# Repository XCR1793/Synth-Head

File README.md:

# Synth Head
To create an open source suit which can be worn by an individual and customised to their will. It also must be constructed in such a way that an average human could build it within a reasonable budget and time. The suit must be modular whilst remaining safe for the user to operate. The software must be easy to configure for any individual and has capability to modify without the need to always reflashing its firmware. The project was created according to this standard however, it has evolved over time to be more of a testing ground for sensors and other features of the like as I will continue this along with other projects I have due to compatibility.

## Overview
This project is always in the works and will be updated. Although regular updates are not possible due to me still being in uni, I will do what I can. This repo is basically a better version of the other repo and a true migration as the old one due to its structure. The reason for it being a new repo rather then just a fix is cause the title changed so the old link wouldn't have worked anyway. The current design is DX which stands for Design 10 as it is the 10th time the base shape has changed, the .3 at the end is an iterator for which version were on.

### Features
* <strong style='color: #99ccff;'>Vacuum Formed Visor</strong> allows the user to see out of a clear shell rather then the previous mesh version which caused chromatic abberation, preventing the true colours of the display from emiting through the visor properly.
* <strong style='color: #99ccff;'>Detachable Substructure</strong> which conformes to the visor ridge provides an easy to modify platform to which different displays, sensors and other modules.
* <strong style='color: #99ccff;'>Builtin Head Restraint</strong> was designed to hold in an average head with relatively high pressure, although the pressure seems like it cause pain, the addition of a foam pad mitigates this and is actually comfortable to wear.
* <strong style='color: #99ccff;'>Silent Slim Jaw Mount</strong> of around 6mm in total thickness is directly integrated to the shell.
* <strong style='color: #99ccff;'>Snoot Sensors</strong> All of the sensors and modules are attached directly into the detachable substructure and can easily be replaced and upgraded as needed, many of which includes: Boop detection, snoot holding detection & IMUs.
* <strong style='color: #99ccff;'>Ventillation</strong> is key to an alive and well user, there are 2 fans located below the tongue which negatively ventillates the user.

### In the works
* The visor edge and mating surface will be changed due to it currently resulting in an uneven edge to edge connection.
* The builtin head restraint will also be upgraded, although the system works it is not the best designed as it is currently difficult to put the pins in place.
* Electronics & other cabling will be hidden in the final release as it is not compact due to the Rushed version built for speed and prototyping rather then stability.
* ARCOS migration is still under play, the entire library is basically being rewritten slowly so it runs faster with more features. The library is currently not accessable as it is privated but it will be released with the release of the synth head 10.3.
* <strong style='color: #ffb3ff;'>Feature Inclusion:</strong> Cable management
* <strong style='color: #ffb3ff;'>Feature Inclusion:</strong> Visor Edge Alignment Upgrade
* <strong style='color: #ffb3ff;'>Feature Inclusion:</strong> Ventillation Upgrade
* <strong style='color: #ffb3ff;'>Feature Inclusion:</strong> Jaw Mount Upgrade (Attached to head restraint)
* <strong style='color: #ffb3ff;'>Feature Inclusion:</strong> Lighter Frame
* <strong style='color: #ffb3ff;'>Feature Inclusion:</strong> Custom PCB (Control Board, Power & Sensors)

### Roadmap
* <strong style='color: #99ff99;'>Milestone:</strong> [Synth Head DX](/Archives/DX/README.md)
* <strong style='color: #99ff99;'>Milestone:</strong> [Synth Head DX.1](/Archives/DX.1/README.md)
* <strong style='color: #99ff99;'>Milestone:</strong> [Synth Head DX.2 Rushed](/Archives/DX.2/README.md)
* <strong style='color: #99ff99;'>Milestone:</strong> [Synth Head DX.3 Rushed](/Archives/DX.3/README.md)
* <strong style='color: #99ff99;'>Milestone:</strong> Properly Structured Github

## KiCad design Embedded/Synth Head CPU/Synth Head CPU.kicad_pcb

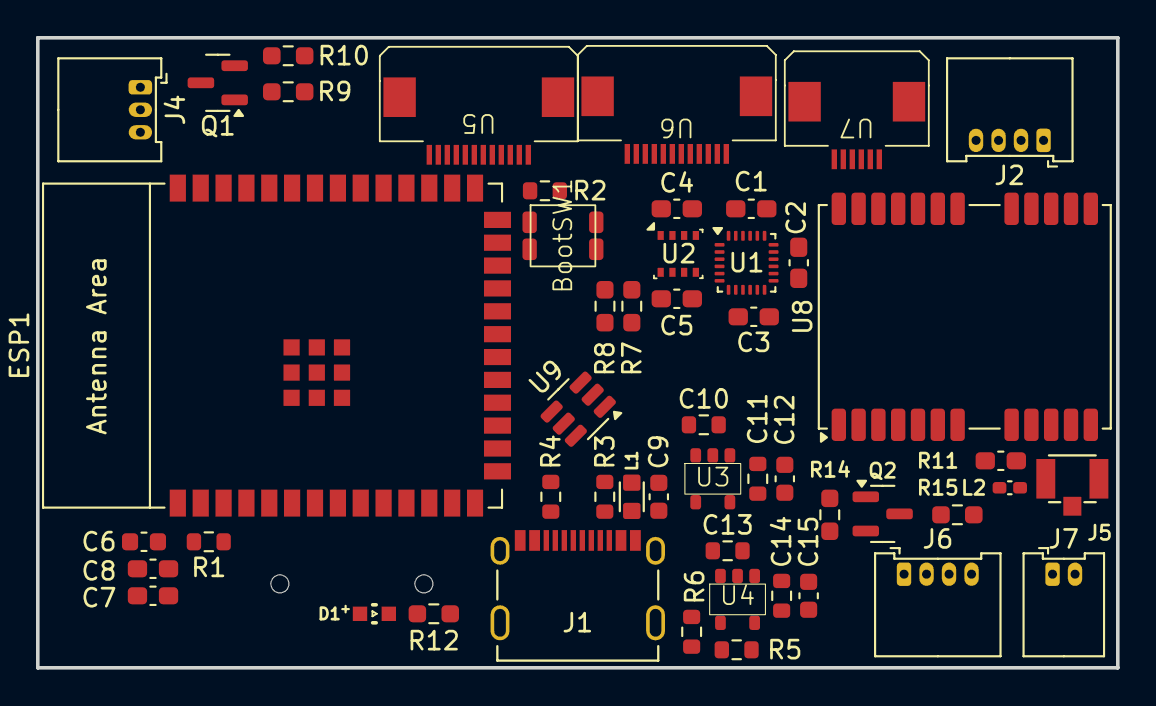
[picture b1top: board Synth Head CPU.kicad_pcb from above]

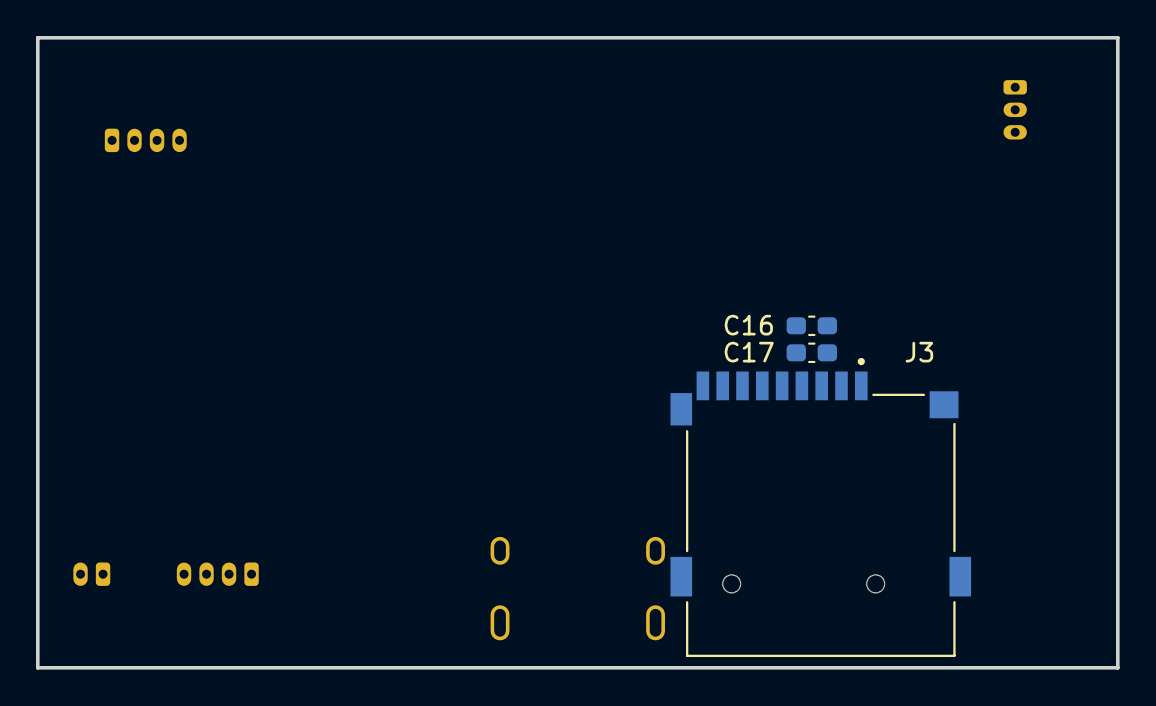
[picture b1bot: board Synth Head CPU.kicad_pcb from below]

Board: 2 copper layers, 60.0 x 35.0 mm, 54 parts (3 on the bottom side), 23 nets, no tracks yet.

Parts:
BootSW1: SW_Push; Button-R-667843
C1, C2, C3, C8, C17: 0.1uF; C_0603_1608Metric_Pad1.08x0.95mm_HandSolder
C4, C5: 100nF; C_0603_1608Metric_Pad1.08x0.95mm_HandSolder
C6: 1uF; C_0603_1608Metric
C7, C16: 22uF; C_0603_1608Metric_Pad1.08x0.95mm_HandSolder
C9, C12, C15: 10uF; C_0603_1608Metric
C10, C11, C13, C14: 1uF; R_0603_1608Metric
D1: WL-SMCW_0603
ESP1: ESP32-S3-WROOM-1
J1: 10171746-00021LF; AMPHENOL_10171746-00021LF
J2: JST [C]; Molex_PicoBlade_53048-0410_1x04_P1.25mm_Horizontal
J3: MSD-1-A; CUI_MSD-1-A
J4: JST [N]; Molex_PicoBlade_53048-0310_1x03_P1.25mm_Horizontal
J5: U.FL-R-SMT-1_10_; HRS_U.FL-R-SMT-1_10_
J6: Pogo JST; Molex_PicoBlade_53048-0410_1x04_P1.25mm_Horizontal
J7: Pogo JST; Molex_PicoBlade_53048-0210_1x02_P1.25mm_Horizontal
L1: MPZ1608S601ATA00; INDC1608X95N
L2: LQG15HS27NJ02; L_0402_1005Metric_Pad0.77x0.64mm_HandSolder
Q1, Q2: BSS138; SOT-23
R1, R2: 10K; R_0603_1608Metric
R3, R4: 5.1K; R_0603_1608Metric
R5: 75K; R_0603_1608Metric
R6: 60K; R_0603_1608Metric
R7, R8, R9, R10, R14, R15: 10K; R_0603_1608Metric_Pad0.98x0.95mm_HandSolder
R11: 10; C_0603_1608Metric_Pad1.08x0.95mm_HandSolder
R12: 65; R_0603_1608Metric_Pad0.98x0.95mm_HandSolder
U1: ICM-20948; InvenSense_QFN-24_3x3mm_P0.4mm
U2: BME280; Bosch_LGA-8_2.5x2.5mm_P0.65mm_ClockwisePinNumbering
U3: AP7366-33W5-7; AP7366
U4: AP7366-W5-7; AP7366
U5: FFC [G]; FFC Aliexpress 0.5mm 12P
U6: FFC [M]; FFC Aliexpress 0.5mm 12P
U7: FFC [K]; FFC Aliexpress 0.5mm 6P
U8: NEO-M8M; ublox_NEO
U9: SRV05-4; SOT-23-6

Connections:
3V3 Jaw LEDS: Q2.2 (S), R14.2
3V3 Neck LEDS: Q1.2 (S), R9.2
+1V8: C1.2, C14.1, C15.1, R5.1, U1.8 (VDDIO), U1.22 (~CS), U4.5 (Vout)
+3V3: C2.1, C4.2, C5.1, C7.1, C8.1, C11.1, C12.1, C16.1, C17.1, D1.2, ESP1.2 (3V3), J3.4 (VDD), Q1.1 (G), Q2.1 (G), R1.1, R2.1, R7.1, R8.1, R9.1, R14.1, U1.13 (VDD), U2.2 (CSB), U2.6 (VDDIO), U2.8 (VDD), U3.5 (Vout), U8.23 (VCC)
+5V: J1.A4_B9 (VBUS_A), J1.B4_A9 (VBUS_B), J2.2, J2.3, J4.2, J7.1, J7.2, L1.1, R10.1, R15.1, U5.5, U5.8, U6.5, U6.8, U9.5 (VP)
/1V8 Regulator/Vin: C9.1, C10.1, C13.1, L1.2, U3.1 (VCC), U3.3 (EN), U4.1 (VCC), U4.3 (EN)
GND: BootSW1.2, C1.1, C2.2, C3.2, C4.1, C5.2, C6.1, C7.2, C8.2, C9.2, C10.2, C11.2, C12.2, C13.2, C14.2, C15.2, C16.2, C17.2, ESP1.1 (GND), ESP1.40 (GND), ESP1.41 (GND), J1.A1_B12 (GND_A), J1.B1_A12 (GND_B), J2.1, J2.4, J3.6 (VSS), J3.G1 (COVER_GND), J3.G2 (COVER_GND__1), J3.G3 (COVER_GND__2), J3.G4 (COVER_GND__3), J4.1, J5.1, J6.1, J6.4, R3.2, R4.2, R6.2, R12.2, U1.9 (SDO/AD0), U1.18 (GND), U1.20 (GND), U2.1 (GND), U2.5 (SDO), U2.7 (GND), U3.2 (GND), U4.2 (GND), U5.1, U5.3, U5.10, U5.12, U6.1, U6.2, U6.3, U6.10, U6.11, U6.12, U7.1, U7.6, U8.7 (VDD_USB), U8.10 (GND), U8.12 (GND), U8.13 (GND), U8.24 (GND), U9.2 (VN)
Jaw LEDS: J6.2, J6.3, Q2.3 (D), R15.2
Neck LEDS: J4.3, Q1.3 (D), R10.2
unnamed: D1.1, R12.1
unnamed: C6.2, ESP1.3 (EN), R1.2
unnamed: BootSW1.1, ESP1.27 (GPIO0/BOOT), R2.2
unnamed: J1.A5 (CC1), R4.1
unnamed: J1.B5 (CC2), R3.1
unnamed: L2.1, R11.2
unnamed: C3.1, U1.10 (REGOUT)
unnamed: R5.2, R6.1, U4.4 (ADJ)
unnamed: J5.2, L2.2, U8.11 (RF_IN)
unnamed: R11.1, U8.9 (VCC_RF)
SCL: R7.2, U1.23 (SCL/SCLK), U2.4 (SCK), U8.19 (SCL/SPI_CLK)
SDA: R8.2, U1.24 (SDA/SDI), U2.3 (SDI), U8.18 (SDA/~SPI_CS)
USB +: ESP1.14 (GPIO20/U1CTS/ADC2_CH9/CLK_OUT1/USB_D+), J1.A6 (DP1), J1.B6 (DP2), U7.3, U9.1 (IO1)
USB -: ESP1.13 (GPIO19/U1RTS/ADC2_CH8/CLK_OUT2/USB_D-), J1.A7 (DN1), J1.B7 (DN2), U7.4, U9.4 (IO3)

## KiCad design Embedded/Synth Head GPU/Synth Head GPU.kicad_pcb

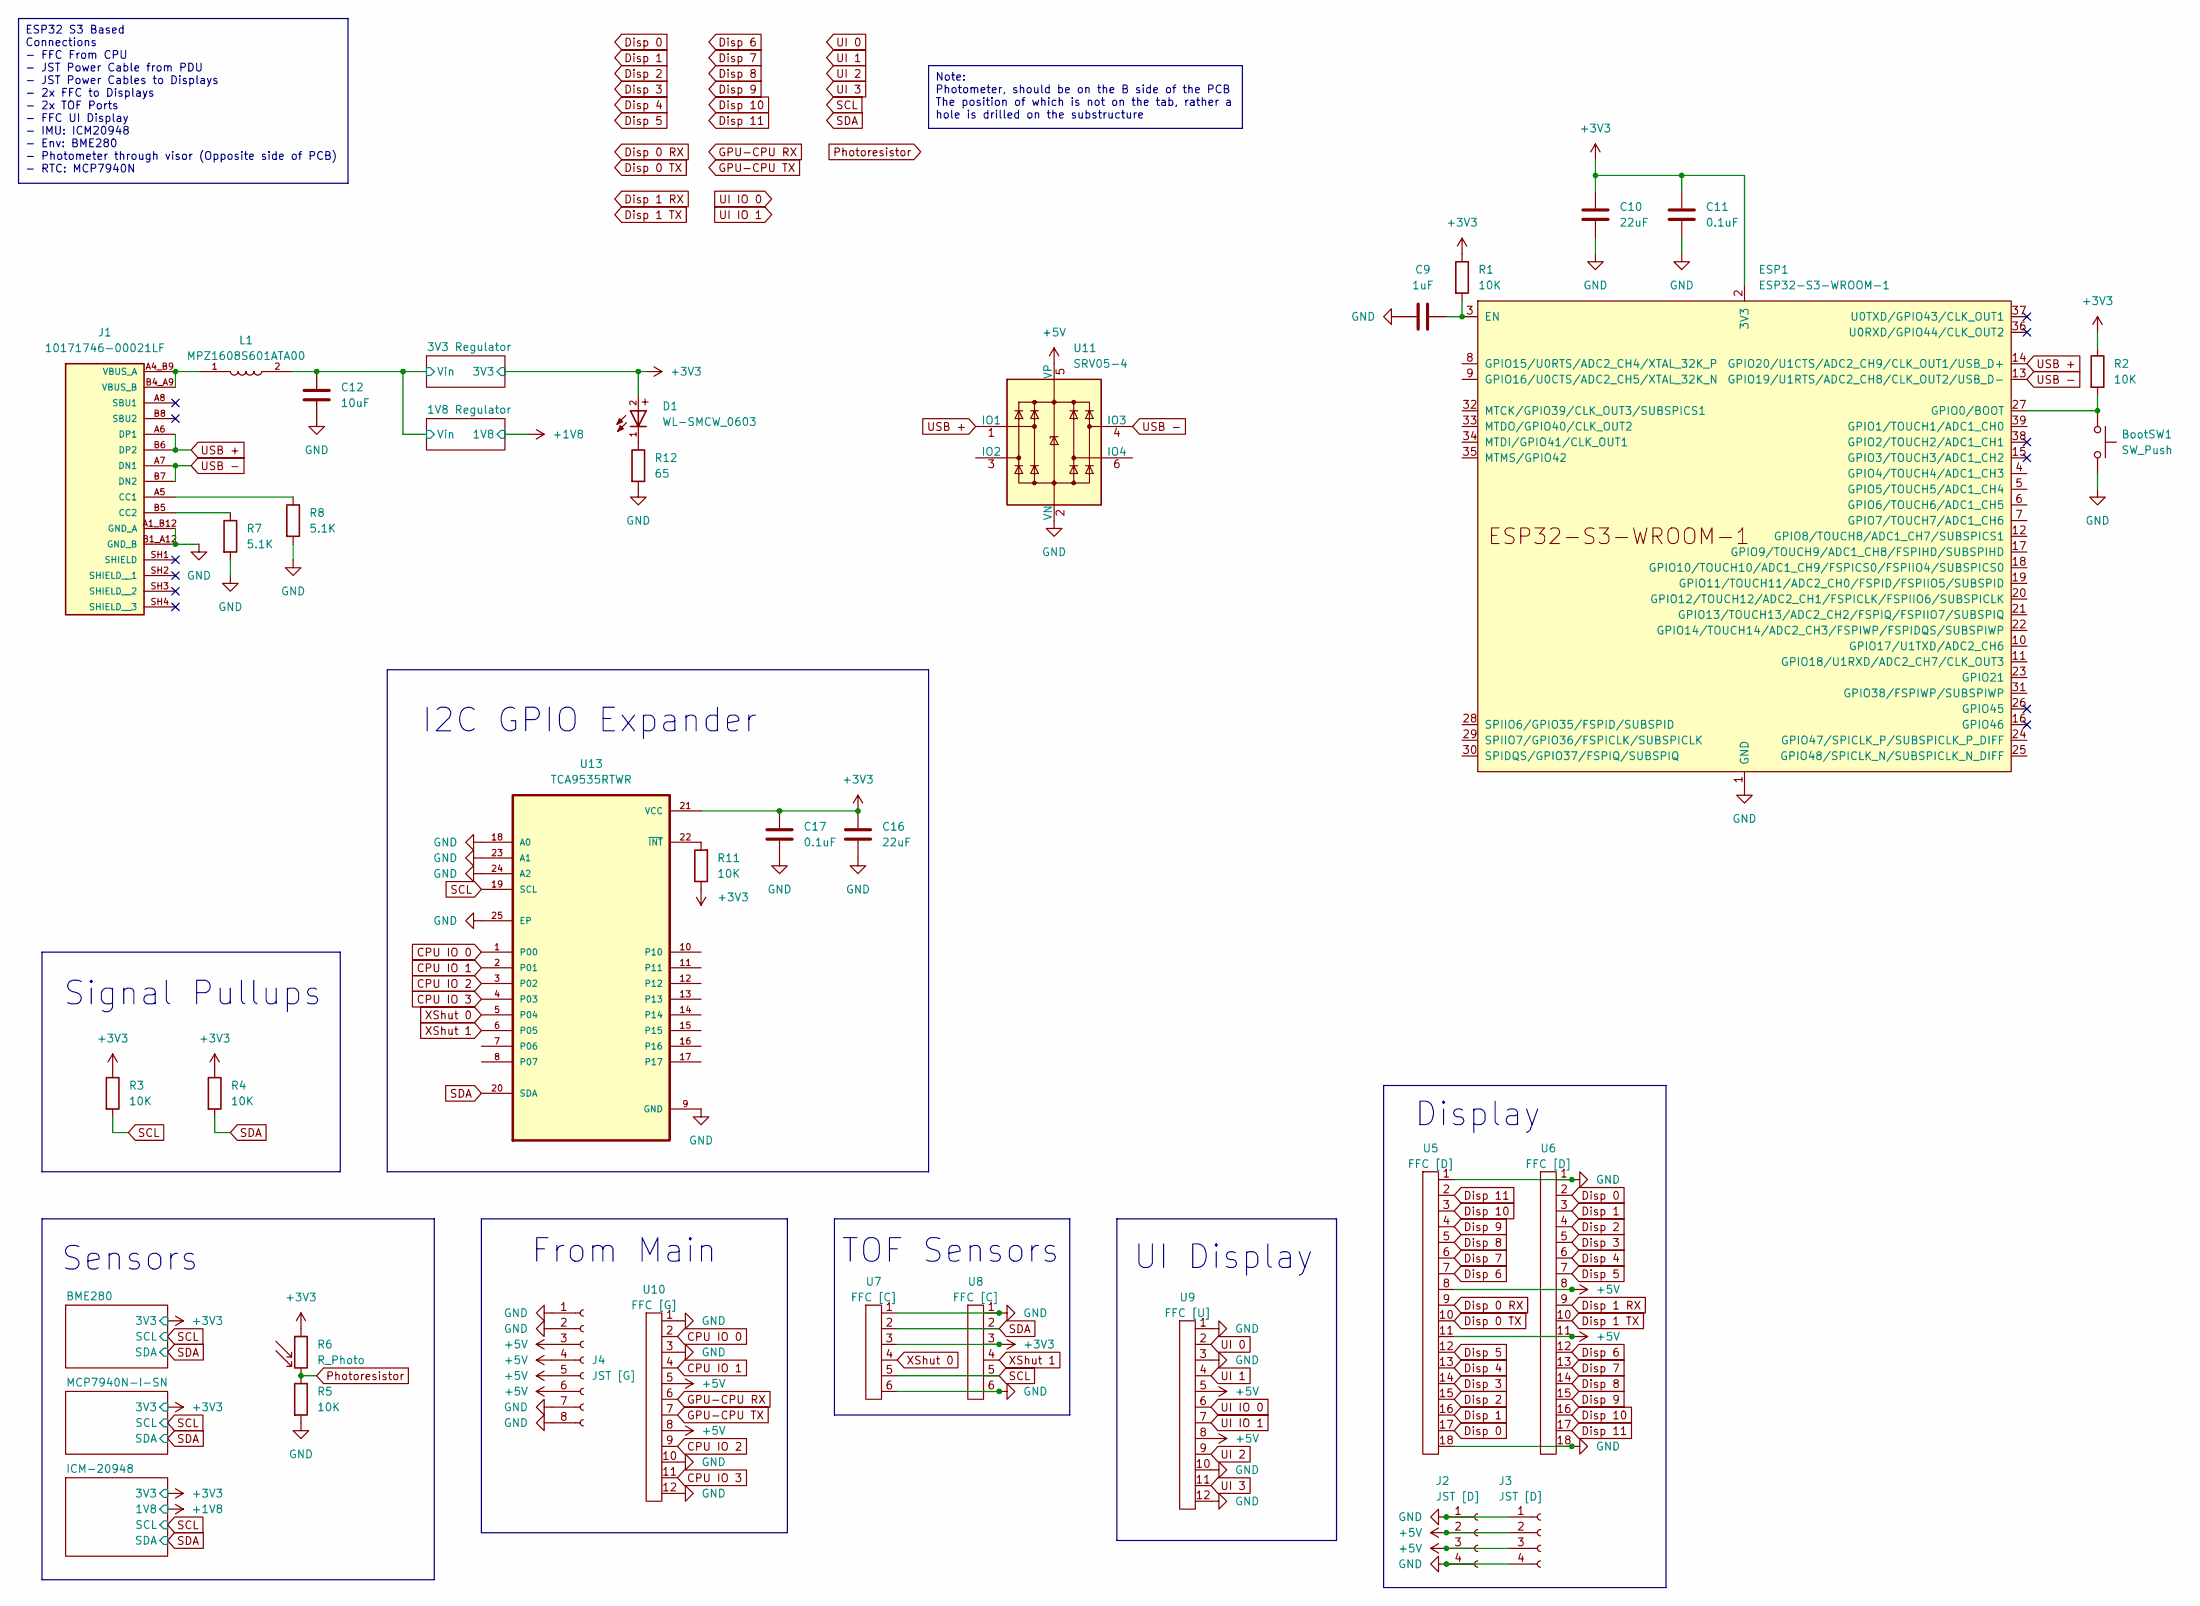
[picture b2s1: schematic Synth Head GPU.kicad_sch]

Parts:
BootSW1: SW_Push; Button-R-667843
C9: 1uF; C_0603_1608Metric
C10, C16: 22uF; C_0603_1608Metric_Pad1.08x0.95mm_HandSolder
C11, C17: 0.1uF; C_0603_1608Metric
C12: 10uF; C_0603_1608Metric
D1: WL-SMCW_0603
ESP1: ESP32-S3-WROOM-1; ESP32-S3-WROOM-1U
J1: 10171746-00021LF; AMPHENOL_10171746-00021LF; PARTREV A
J2, J3: JST [D]; Molex_PicoBlade_53048-0410_1x04_P1.25mm_Horizontal
J4: JST [G]; PinHeader_1x08_P2.54mm_Horizontal
L1: MPZ1608S601ATA00; INDC1608X95N
R1, R2, R11: 10K; R_0603_1608Metric
R3, R4, R5: 10K; R_0603_1608Metric_Pad0.98x0.95mm_HandSolder
R6: R_Photo; Photoresistor Aliexpress
R7, R8: 5.1K; R_0603_1608Metric
R12: 65; R_0603_1608Metric_Pad0.98x0.95mm_HandSolder
U5, U6: FFC [D]; FFC Aliexpress 0.5mm 18P
U7, U8: FFC [C]; FFC Aliexpress 0.5mm 6P
U9: FFC [U]; FFC Aliexpress 0.5mm 12P
U10: FFC [G]; FFC Aliexpress 0.5mm 12P
U11: SRV05-4; SOT-23-6
U13: TCA9535RTWR; QFN50P400X400X80-25N

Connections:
+3V3: C10.1, C11.1, C16.1, C17.1, D1.2, ESP1.2 (3V3), R1.1, R2.1, R3.1, R4.1, R6.1, R11.1, U7.3, U8.3, U13.21 (VCC); also elsewhere on the board
+5V: J2.2, J2.3, J3.2, J3.3, J4.3, J4.4, J4.5, J4.6, U5.8, U5.11, U6.8, U6.11, U9.5, U9.8, U10.5, U10.8, U11.5 (VP)
/1V8 Regulator/Vin: C12.1, L1.2; also elsewhere on the board
CPU IO 0: U10.2, U13.1 (P00)
CPU IO 1: U10.4, U13.2 (P01)
CPU IO 2: U10.9, U13.3 (P02)
CPU IO 3: U10.11, U13.4 (P03)
Disp 0: U5.17, U6.2
Disp 0 RX: U5.9
Disp 0 TX: U5.10
Disp 1: U5.16, U6.3
Disp 1 RX: U6.9
Disp 1 TX: U6.10
Disp 2: U5.15, U6.4
Disp 3: U5.14, U6.5
Disp 4: U5.13, U6.6
Disp 5: U5.12, U6.7
Disp 6: U5.7, U6.12
Disp 7: U5.6, U6.13
Disp 8: U5.5, U6.14
Disp 9: U5.4, U6.15
Disp 10: U5.3, U6.16
Disp 11: U5.2, U6.17
GND: BootSW1.2, C9.1, C10.2, C11.2, C12.2, C16.2, C17.2, ESP1.1 (GND), ESP1.40 (GND), ESP1.41 (GND), J1.A1_B12 (GND_A), J1.B1_A12 (GND_B), J2.1, J2.4, J3.1, J3.4, J4.1, J4.2, J4.7, J4.8, R5.2, R7.2, R8.2, R12.2, U5.1, U5.18, U6.1, U6.18, U7.1, U7.6, U8.1, U8.6, U9.1, U9.3, U9.10, U9.12, U10.1, U10.3, U10.10, U10.12, U11.2 (VN), U13.9 (GND), U13.18 (A0), U13.23 (A1), U13.24 (A2), U13.25 (EP); also elsewhere on the board
GPU-CPU RX: U10.6
GPU-CPU TX: U10.7
unnamed: D1.1, R12.1
unnamed: C9.2, ESP1.3 (EN), R1.2
unnamed: BootSW1.1, ESP1.27 (GPIO0/BOOT), R2.2
unnamed: J1.A5 (CC1), R8.1
unnamed: J1.B5 (CC2), R7.1
unnamed: J1.A4_B9 (VBUS_A), J1.B4_A9 (VBUS_B), L1.1
unnamed: R11.2, U13.22 (~INT)
Photoresistor: R5.1, R6.2
SCL: R3.2, U7.5, U8.5, U13.19 (SCL); also elsewhere on the board
SDA: R4.2, U7.2, U8.2, U13.20 (SDA); also elsewhere on the board
UI 0: U9.2
UI 1: U9.4
UI 2: U9.9
UI 3: U9.11
UI IO 0: U9.6
UI IO 1: U9.7
USB +: ESP1.14 (GPIO20/U1CTS/ADC2_CH9/CLK_OUT1/USB_D+), J1.A6 (DP1), J1.B6 (DP2), U11.1 (IO1)
USB -: ESP1.13 (GPIO19/U1RTS/ADC2_CH8/CLK_OUT2/USB_D-), J1.A7 (DN1), J1.B7 (DN2), U11.4 (IO3)
XShut 0: U7.4, U13.5 (P04)
XShut 1: U8.4, U13.6 (P05)

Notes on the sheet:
ESP32 S3 Based Connections - FFC From CPU - JST Power Cable from PDU - JST Power Cables to Displays - 2x FFC to Displays - 2x TOF Ports - FFC UI Display - IMU: ICM20948 - Env: BME280 - Photometer through visor (Opposite side of PCB) - RTC: MCP7940N
Note: Photometer, should be on the B side of the PCB The position of which is not on the tab, rather a hole is drilled on the substructure
Signal Pullups
I2C GPIO Expander
TOF Sensors
From Main
Display
UI Display
Sensors

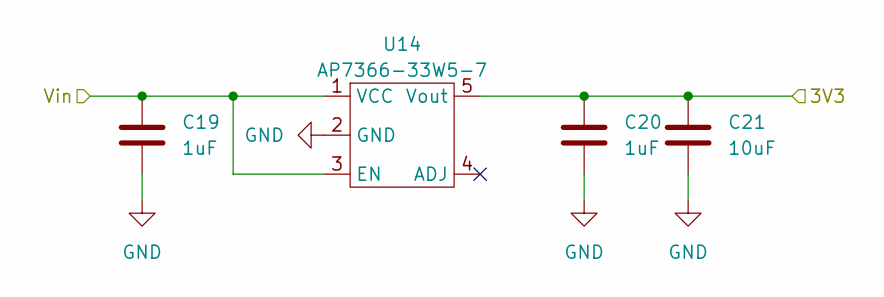
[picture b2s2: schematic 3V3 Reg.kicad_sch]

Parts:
C19, C20: 1uF; R_0603_1608Metric
C21: 10uF; C_0603_1608Metric
U14: AP7366-33W5-7; AP7366

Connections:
+3V3: C20.1, C21.1, U14.5 (Vout); also elsewhere on the board
/1V8 Regulator/Vin: C19.1, U14.1 (VCC), U14.3 (EN); also elsewhere on the board
GND: C19.2, C20.2, C21.2, U14.2 (GND); also elsewhere on the board

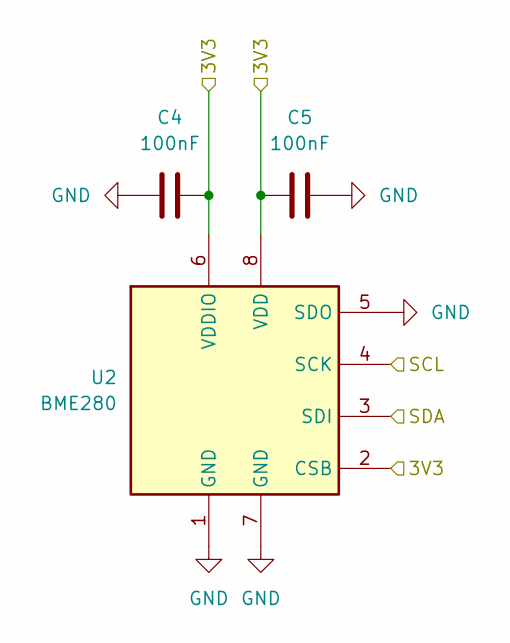
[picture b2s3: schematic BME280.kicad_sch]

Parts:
C4, C5: 100nF
U2: BME280; Bosch_LGA-8_2.5x2.5mm_P0.65mm_ClockwisePinNumbering

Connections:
+3V3: C4.2, C5.1, U2.2 (CSB), U2.6 (VDDIO), U2.8 (VDD); also elsewhere on the board
GND: C4.1, C5.2, U2.1 (GND), U2.5 (SDO), U2.7 (GND); also elsewhere on the board
SCL: U2.4 (SCK); also elsewhere on the board
SDA: U2.3 (SDI); also elsewhere on the board

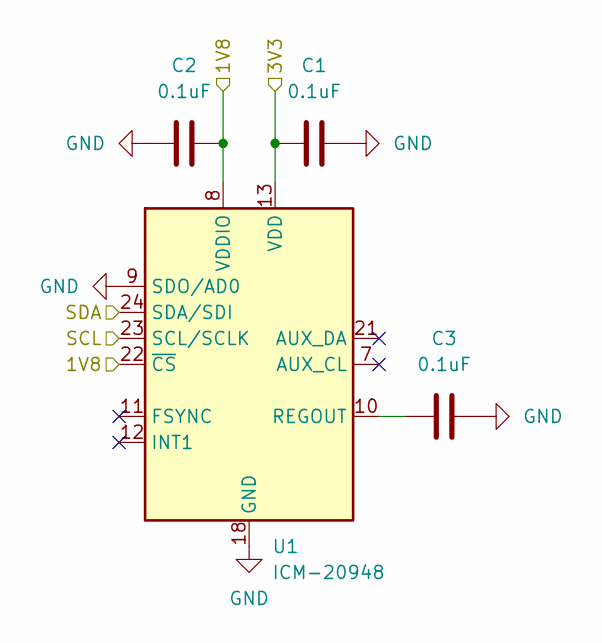
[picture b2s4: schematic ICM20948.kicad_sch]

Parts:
C1, C2, C3: 0.1uF
U1: ICM-20948; InvenSense_QFN-24_3x3mm_P0.4mm

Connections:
+1V8: C2.2, U1.8 (VDDIO), U1.22 (~CS); also elsewhere on the board
+3V3: C1.1, U1.13 (VDD); also elsewhere on the board
GND: C1.2, C2.1, C3.2, U1.9 (SDO/AD0), U1.18 (GND), U1.20 (GND); also elsewhere on the board
unnamed: C3.1, U1.10 (REGOUT)
SCL: U1.23 (SCL/SCLK); also elsewhere on the board
SDA: U1.24 (SDA/SDI); also elsewhere on the board

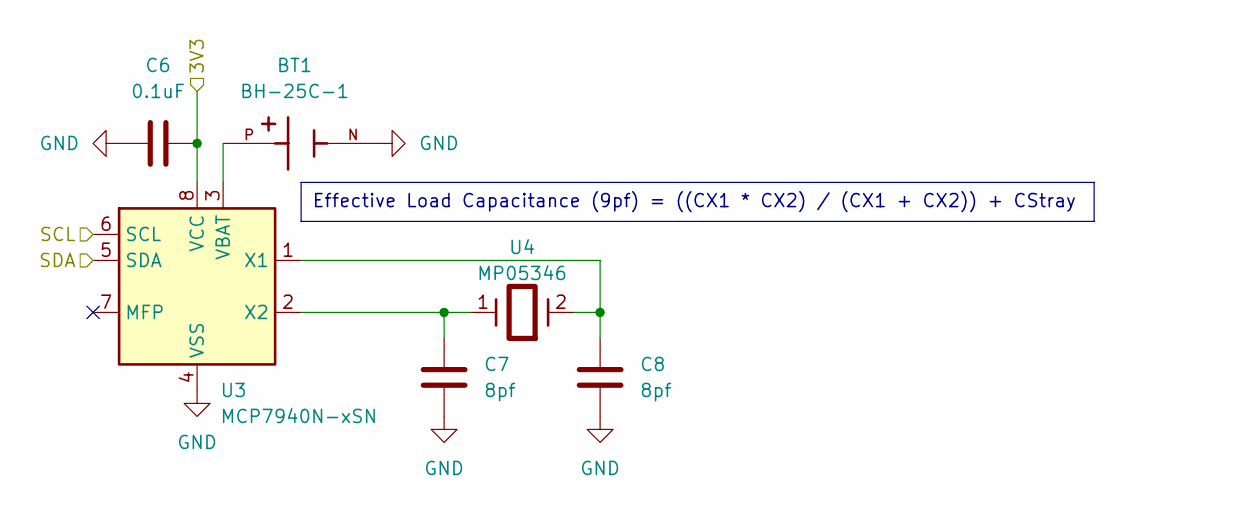
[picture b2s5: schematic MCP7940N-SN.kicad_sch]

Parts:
BT1: BH-25C-1; BAT_BH-25C-1
C6: 0.1uF; C_0603_1608Metric_Pad1.08x0.95mm_HandSolder
C7, C8: 8pf; C_0603_1608Metric_Pad1.08x0.95mm_HandSolder
U3: MCP7940N-xSN; SOIC-8_3.9x4.9mm_P1.27mm
U4: MP05346

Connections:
+3V3: C6.2, U3.8 (VCC); also elsewhere on the board
GND: BT1.N, C6.1, C7.2, C8.2, U3.4 (VSS); also elsewhere on the board
unnamed 33: BT1.P, U3.3 (VBAT); also elsewhere on the board
unnamed: C8.1, U3.1 (X1), U4.2
unnamed: C7.1, U3.2 (X2), U4.1
SCL: U3.6 (SCL); also elsewhere on the board
SDA: U3.5 (SDA); also elsewhere on the board

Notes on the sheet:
Effective Load Capacitance (9pf) = ((CX1 * CX2) / (CX1 + CX2)) + CStray

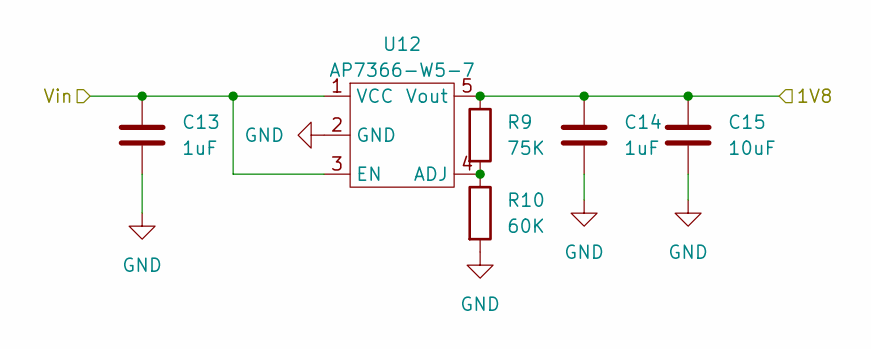
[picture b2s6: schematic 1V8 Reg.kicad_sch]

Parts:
C13, C14: 1uF; R_0603_1608Metric
C15: 10uF; C_0603_1608Metric
R9: 75K; R_0603_1608Metric
R10: 60K; R_0603_1608Metric
U12: AP7366-W5-7; AP7366

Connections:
+1V8: C14.1, C15.1, R9.1, U12.5 (Vout); also elsewhere on the board
/1V8 Regulator/Vin: C13.1, U12.1 (VCC), U12.3 (EN); also elsewhere on the board
GND: C13.2, C14.2, C15.2, R10.2, U12.2 (GND); also elsewhere on the board
unnamed: R9.2, R10.1, U12.4 (ADJ)

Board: 2 copper layers, 55 parts (19 on the bottom side), 40 nets, no tracks yet.

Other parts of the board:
J5: Coin Cell; PinHeader_1x02_P2.54mm_Vertical

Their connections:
GND: J5.2; also elsewhere on the board
unnamed 33: J5.1; also elsewhere on the board

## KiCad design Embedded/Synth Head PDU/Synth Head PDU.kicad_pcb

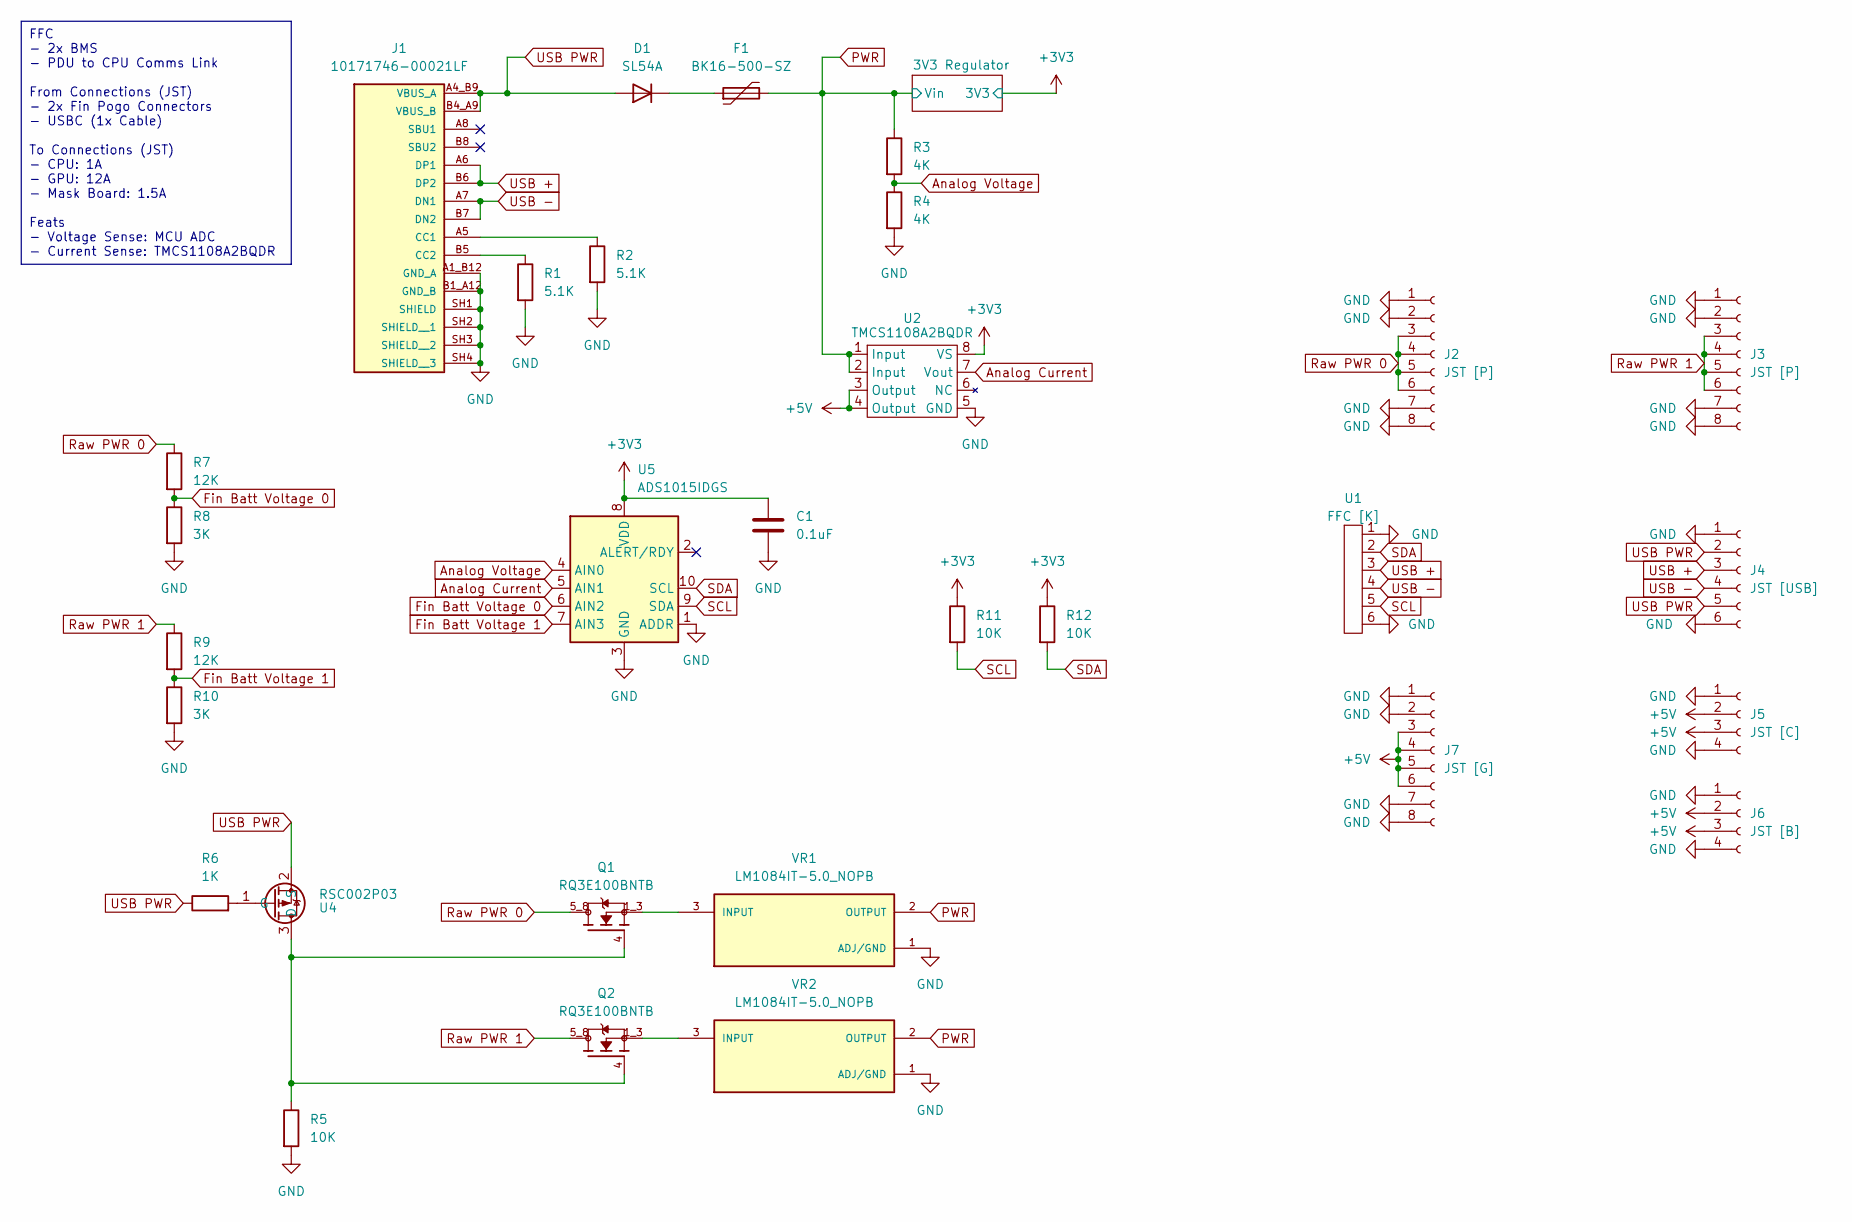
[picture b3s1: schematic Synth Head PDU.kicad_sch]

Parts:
C1: 0.1uF; C_0603_1608Metric_Pad1.08x0.95mm_HandSolder
D1: SL54A; D_SMA-SMB_Universal_Handsoldering
F1: BK16-500-SZ; Fuse_Bourns_MF-RHT500
J1: 10171746-00021LF; AMPHENOL_10171746-00021LF; PARTREV A
J2, J3: JST [P]; PinHeader_1x08_P2.54mm_Vertical
J4: JST [USB]; PinHeader_1x06_P2.54mm_Vertical
J5: JST [C]; PinHeader_1x04_P2.54mm_Vertical
J6: JST [B]; PinHeader_1x04_P2.54mm_Vertical
J7: JST [G]; PinHeader_1x08_P2.54mm_Vertical
Q1, Q2: RQ3E100BNTB; TRANS_RQ3E100BNTB; PARTREV B
R1, R2: 5.1K; R_0603_1608Metric
R3, R4: 4K; R_0603_1608Metric_Pad0.98x0.95mm_HandSolder
R5: 10K; R_0603_1608Metric
R6: 1K; R_0603_1608Metric_Pad0.98x0.95mm_HandSolder
R7, R9: 12K; C_0603_1608Metric_Pad1.08x0.95mm_HandSolder
R8, R10: 3K; C_0603_1608Metric_Pad1.08x0.95mm_HandSolder
R11, R12: 10K; R_0603_1608Metric_Pad0.98x0.95mm_HandSolder
U1: FFC [K]; FFC Aliexpress 0.5mm 6P
U2: TMCS1108A2BQDR; SOIC-8_3.9x4.9mm_P1.27mm
U4: RSC002P03
U5: ADS1015IDGS; TSSOP-10_3x3mm_P0.5mm
VR1, VR2: LM1084IT-5.0_NOPB; TO254P1054X470X1955-3; PARTREV G

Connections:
+3V3: C1.1, R11.1, R12.1, U2.8 (VS), U5.8 (VDD); also elsewhere on the board
+5V: J5.2, J5.3, J6.2, J6.3, J7.3, J7.4, J7.5, J7.6, U2.3 (Output), U2.4 (Output)
Analog Current: U2.7 (Vout), U5.5 (AIN1)
Analog Voltage: R3.2, R4.1, U5.4 (AIN0)
Fin Batt Voltage 0: R7.2, R8.1, U5.6 (AIN2)
Fin Batt Voltage 1: R9.2, R10.1, U5.7 (AIN3)
GND: C1.2, J1.A1_B12 (GND_A), J1.B1_A12 (GND_B), J1.SH1 (SHIELD), J1.SH2 (SHIELD__1), J1.SH3 (SHIELD__2), J1.SH4 (SHIELD__3), J2.1, J2.2, J2.7, J2.8, J3.1, J3.2, J3.7, J3.8, J4.1, J4.6, J5.1, J5.4, J6.1, J6.4, J7.1, J7.2, J7.7, J7.8, R1.2, R2.2, R4.2, R5.2, R8.2, R10.2, U1.1, U1.6, U2.5 (GND), U5.1 (ADDR), U5.3 (GND), VR1.1 (ADJ/GND), VR2.1 (ADJ/GND); also elsewhere on the board
unnamed: D1.1 (K), F1.1
unnamed: J1.A5 (CC1), R2.1
unnamed: J1.B5 (CC2), R1.1
unnamed: Q1.4, Q2.4, R5.1, U4.3 (D)
unnamed: R6.2, U4.1 (G)
unnamed: Q1.1_3, VR1.3 (INPUT)
unnamed: Q2.1_3, VR2.3 (INPUT)
PWR: F1.2, R3.1, U2.1 (Input), U2.2 (Input), VR1.2 (OUTPUT), VR2.2 (OUTPUT); also elsewhere on the board
Raw PWR 0: J2.3, J2.4, J2.5, J2.6, Q1.5_8, R7.1
Raw PWR 1: J3.3, J3.4, J3.5, J3.6, Q2.5_8, R9.1
SCL: R11.2, U1.5, U5.9 (SDA)
SDA: R12.2, U1.2, U5.10 (SCL)
USB +: J1.A6 (DP1), J1.B6 (DP2), J4.3, U1.3
USB -: J1.A7 (DN1), J1.B7 (DN2), J4.4, U1.4
USB PWR: D1.2 (A), J1.A4_B9 (VBUS_A), J1.B4_A9 (VBUS_B), J4.2, J4.5, R6.1, U4.2 (S)

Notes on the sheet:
FFC - 2x BMS - PDU to CPU Comms Link From Connections (JST) - 2x Fin Pogo Connectors - USBC (1x Cable) To Connections (JST) - CPU: 1A - GPU: 12A - Mask Board: 1.5A Feats - Voltage Sense: MCU ADC - Current Sense: TMCS1108A2BQDR

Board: 2 copper layers, 34 parts (0 on the bottom side), 22 nets, no tracks yet.

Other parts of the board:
C2, C3: 1uF; R_0603_1608Metric
C4: 10uF; C_0603_1608Metric
U3: AP7366-33W5-7; AP7366

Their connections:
+3V3: C3.1, C4.1, U3.5 (Vout); also elsewhere on the board
GND: C2.2, C3.2, C4.2, U3.2 (GND); also elsewhere on the board
PWR: C2.1, U3.1 (VCC), U3.3 (EN); also elsewhere on the board

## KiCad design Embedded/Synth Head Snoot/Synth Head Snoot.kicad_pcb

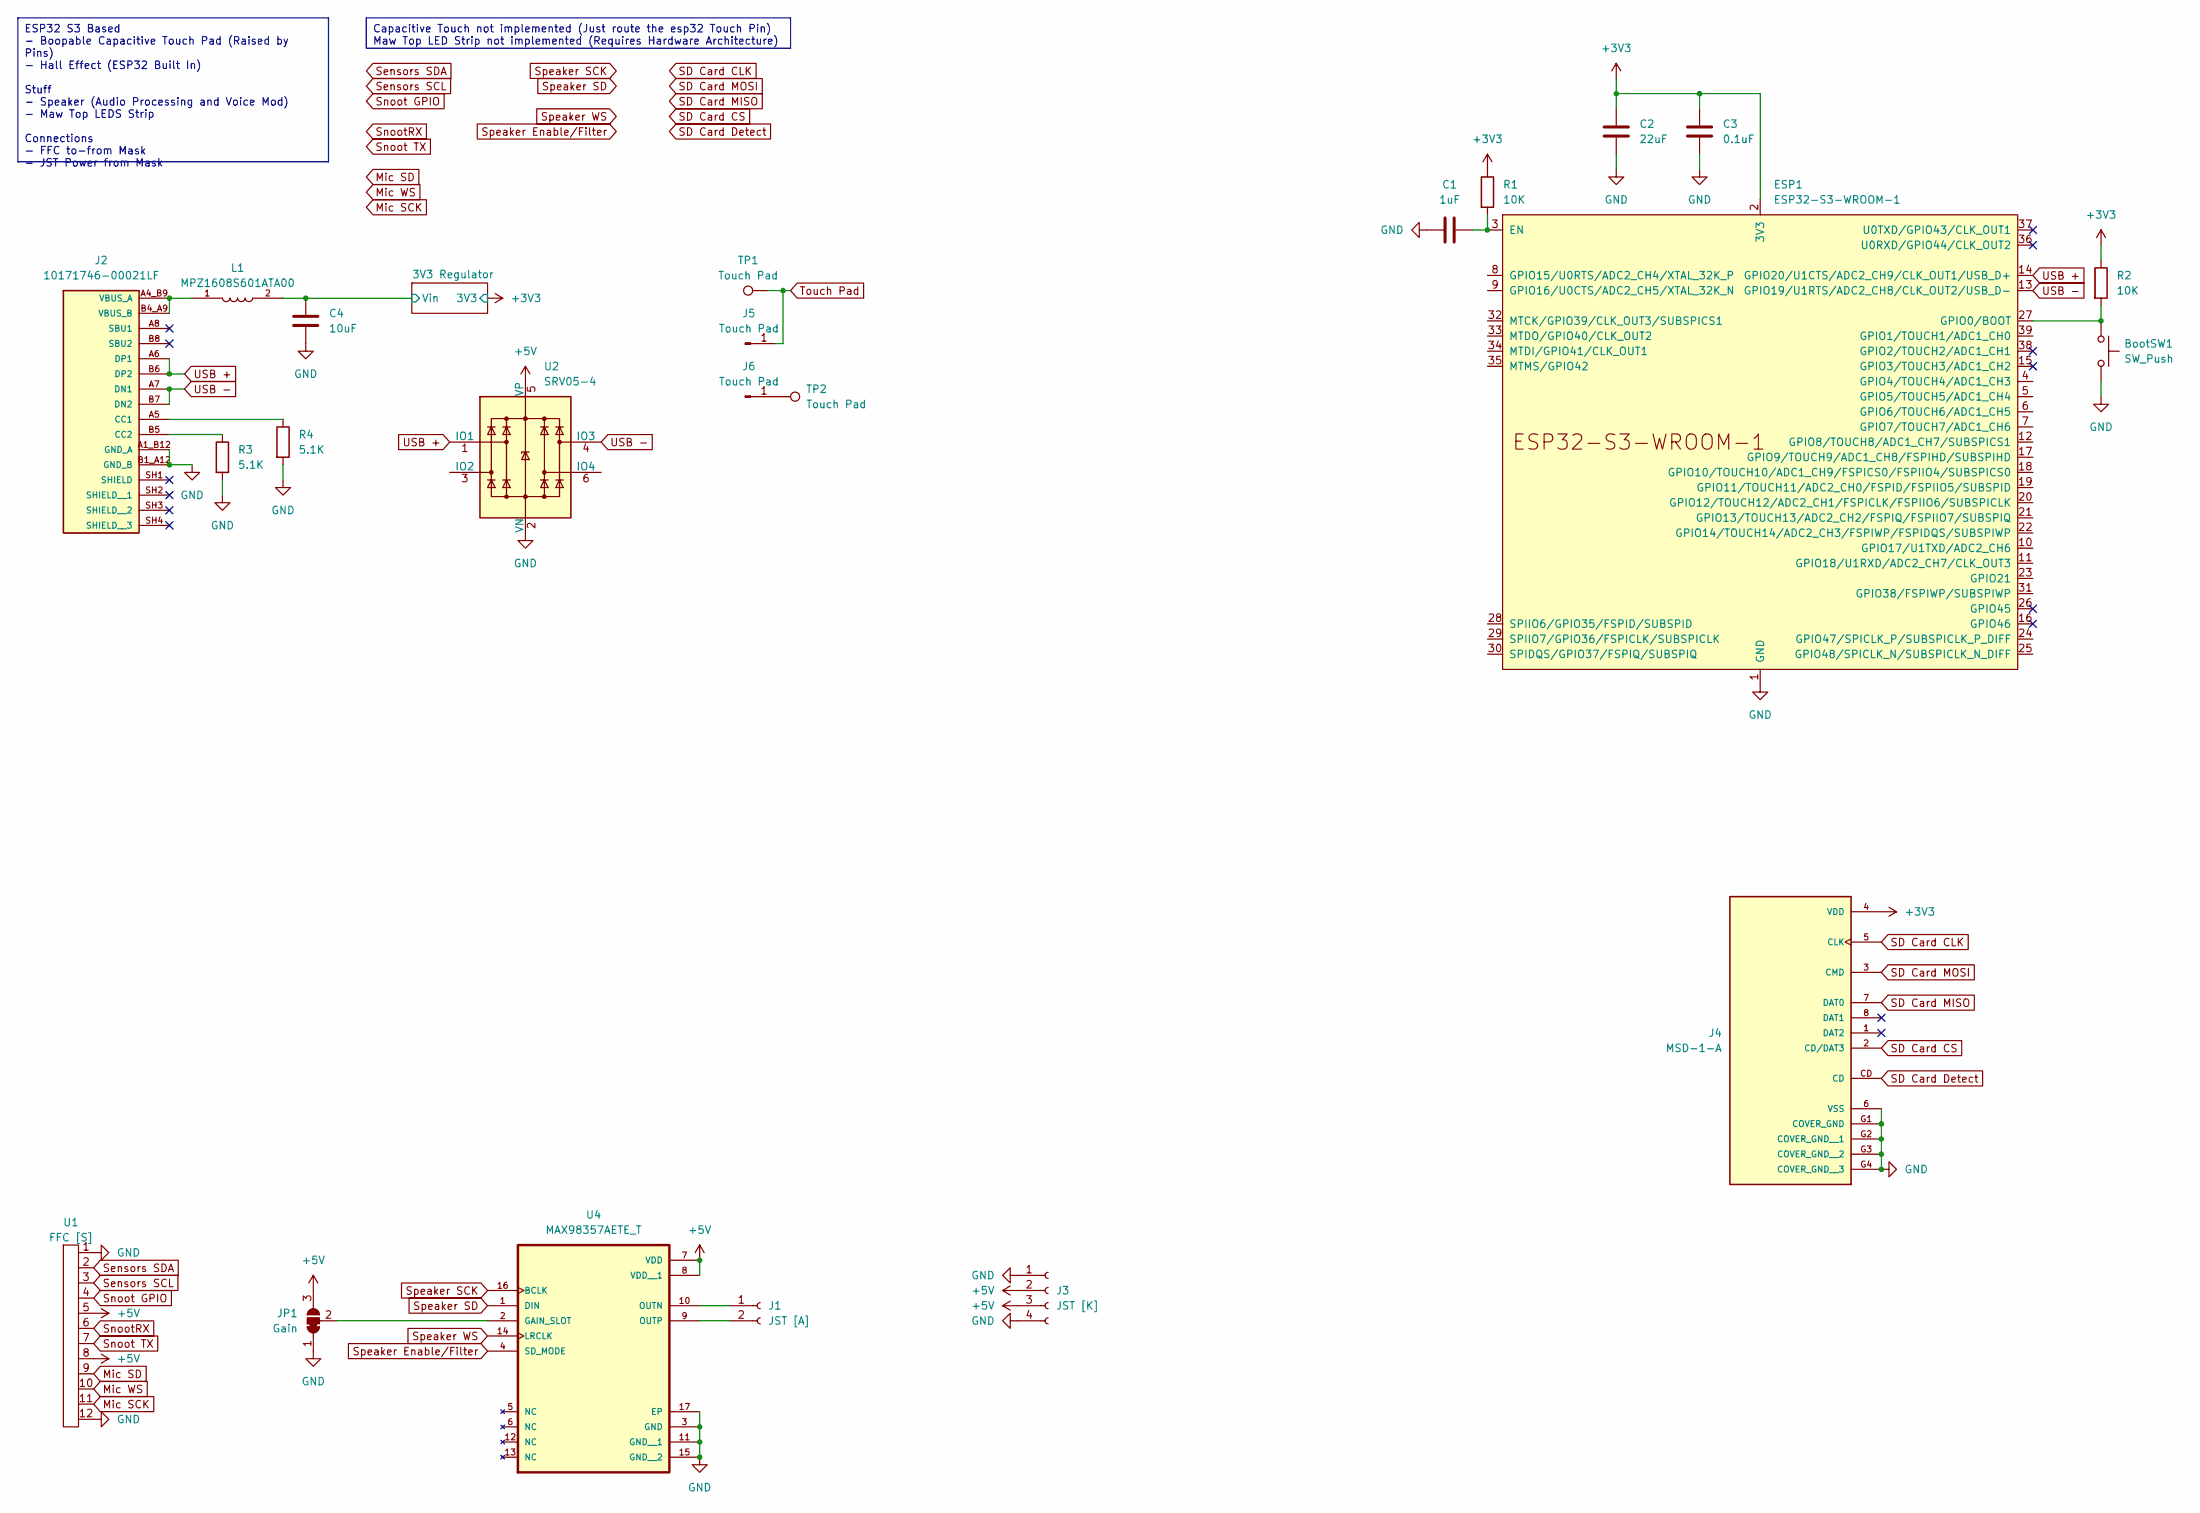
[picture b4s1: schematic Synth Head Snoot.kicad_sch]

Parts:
BootSW1: SW_Push; Button-R-667843
C1: 1uF; C_0603_1608Metric
C2: 22uF; C_0603_1608Metric_Pad1.08x0.95mm_HandSolder
C3: 0.1uF; C_0603_1608Metric
C4: 10uF; C_0603_1608Metric
ESP1: ESP32-S3-WROOM-1; ESP32-S3-WROOM-1U
J1: JST [A]; Molex_PicoBlade_53048-0210_1x02_P1.25mm_Horizontal
J2: 10171746-00021LF; AMPHENOL_10171746-00021LF; PARTREV A
J3: JST [K]; Molex_PicoBlade_53048-0410_1x04_P1.25mm_Horizontal
J4: MSD-1-A; CUI_MSD-1-A; PARTREV 1.0
J5, J6: Touch Pad; PinHeader_1x01_P2.54mm_Vertical
JP1: Gain; SolderJumper-3_P1.3mm_Bridged12_Pad1.0x1.5mm_NumberLabels
L1: MPZ1608S601ATA00; INDC1608X95N
R1, R2: 10K; R_0603_1608Metric
R3, R4: 5.1K; R_0603_1608Metric
TP1, TP2: Touch Pad; TestPoint_Pad_D2.0mm
U1: FFC [S]; FFC Aliexpress 0.5mm 12P
U2: SRV05-4; SOT-23-6
U4: MAX98357AETE_T; QFN50P300X300X80-17N

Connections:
+3V3: C2.1, C3.1, ESP1.2 (3V3), J4.4 (VDD), R1.1, R2.1; also elsewhere on the board
+5V: J3.2, J3.3, JP1.3 (B), U1.5, U1.8, U2.5 (VP), U4.7 (VDD), U4.8 (VDD__1)
/3V3 Regulator/Vin: C4.1, L1.2; also elsewhere on the board
GND: BootSW1.2, C1.1, C2.2, C3.2, C4.2, ESP1.1 (GND), ESP1.40 (GND), ESP1.41 (GND), J2.A1_B12 (GND_A), J2.B1_A12 (GND_B), J3.1, J3.4, J4.6 (VSS), J4.G1 (COVER_GND), J4.G2 (COVER_GND__1), J4.G3 (COVER_GND__2), J4.G4 (COVER_GND__3), JP1.1 (A), R3.2, R4.2, U1.1, U1.12, U2.2 (VN), U4.3 (GND), U4.11 (GND__1), U4.15 (GND__2), U4.17 (EP); also elsewhere on the board
Mic SCK: U1.11
Mic SD: U1.9
Mic WS: U1.10
unnamed: C1.2, ESP1.3 (EN), R1.2
unnamed: BootSW1.1, ESP1.27 (GPIO0/BOOT), R2.2
unnamed: J1.1, U4.10 (OUTN)
unnamed: J1.2, U4.9 (OUTP)
unnamed: J2.A5 (CC1), R4.1
unnamed: J2.B5 (CC2), R3.1
unnamed: J2.A4_B9 (VBUS_A), J2.B4_A9 (VBUS_B), L1.1
unnamed: J6.1, TP2.1
unnamed: JP1.2 (C), U4.2 (GAIN_SLOT)
SD Card CLK: J4.5 (CLK)
SD Card CS: J4.2 (CD/DAT3)
SD Card Detect: J4.CD
SD Card MISO: J4.7 (DAT0)
SD Card MOSI: J4.3 (CMD)
Sensors SCL: U1.3
Sensors SDA: U1.2
Snoot GPIO: U1.4
Snoot TX: U1.7
SnootRX: U1.6
Speaker Enable/Filter: U4.4 (SD_MODE)
Speaker SCK: U4.16 (BCLK)
Speaker SD: U4.1 (DIN)
Speaker WS: U4.14 (LRCLK)
Touch Pad: J5.1, TP1.1
USB +: ESP1.14 (GPIO20/U1CTS/ADC2_CH9/CLK_OUT1/USB_D+), J2.A6 (DP1), J2.B6 (DP2), U2.1 (IO1)
USB -: ESP1.13 (GPIO19/U1RTS/ADC2_CH8/CLK_OUT2/USB_D-), J2.A7 (DN1), J2.B7 (DN2), U2.4 (IO3)

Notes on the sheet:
Capacitive Touch not implemented (Just route the esp32 Touch Pin) Maw Top LED Strip not implemented (Requires Hardware Architecture)
ESP32 S3 Based - Boopable Capacitive Touch Pad (Raised by Pins) - Hall Effect (ESP32 Built In) Stuff - Speaker (Audio Processing and Voice Mod) - Maw Top LEDS Strip Connections - FFC to-from Mask - JST Power from Mask
